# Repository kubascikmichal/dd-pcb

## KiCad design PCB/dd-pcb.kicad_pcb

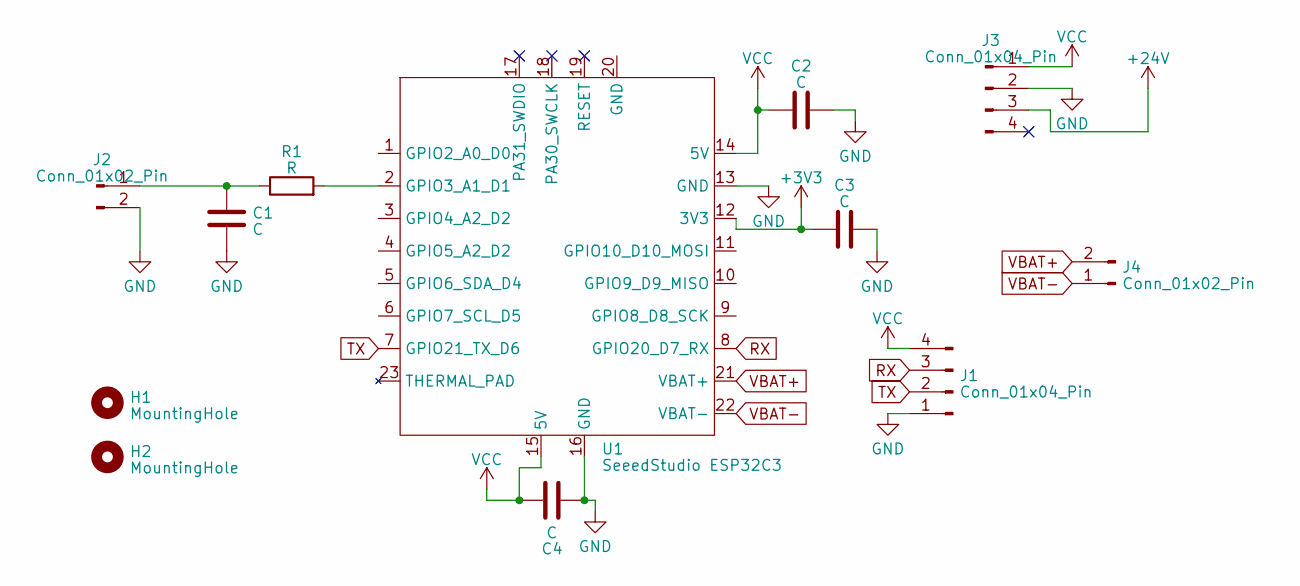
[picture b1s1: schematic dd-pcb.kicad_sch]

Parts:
C1, C2, C3, C4: C; C_0805_2012Metric
H1, H2: MountingHole; MountingHole_2.2mm_M2
J1, J3: Conn_01x04_Pin; PinSocket_1x04_P2.54mm_Vertical
J2, J4: Conn_01x02_Pin; PinSocket_1x02_P2.54mm_Vertical
R1: R; R_0805_2012Metric
U1: SeeedStudio ESP32C3; XIAO-ESP32C3-14P-2.54-21X17.8MM

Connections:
+3V3: C3.1, U1.12 (3V3)
+24V: J3.3
GND: C1.2, C2.2, C3.2, C4.2, J1.1, J2.2, J3.2, U1.13 (GND), U1.16 (GND)
unnamed: C1.1, J2.1, R1.1
unnamed: R1.2, U1.2 (GPIO3_A1_D1)
RX: J1.3, U1.8 (GPIO20_D7_RX)
TX: J1.2, U1.7 (GPIO21_TX_D6)
VBAT+: J4.2, U1.21 (VBAT+)
VBAT-: J4.1, U1.22 (VBAT-)
VCC: C2.1, C4.1, J1.4, J3.1, U1.14 (5V), U1.15 (5V)

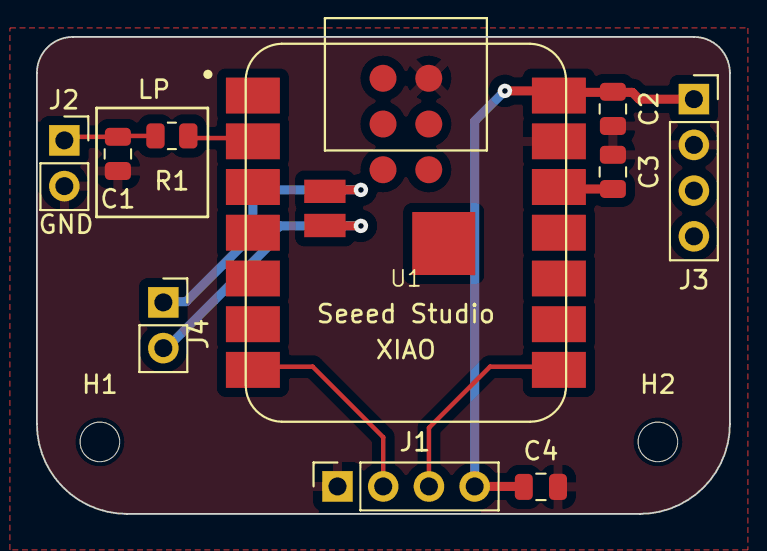
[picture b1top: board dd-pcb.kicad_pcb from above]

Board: 2 copper layers, 38.5 x 26.5 mm, 12 parts (0 on the bottom side), 9 nets.

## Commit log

2024-09-26 Changed components
